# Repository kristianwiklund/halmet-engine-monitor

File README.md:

# Disclaimer

Completely untested, and 99% was written by Claude - I will do more work on this including QA
once spring arrives and it is possible to do work in the actual boat again.

# HALMET Marine Engine & Tank Monitor

Firmware for the [Hat Labs HALMET](https://docs.hatlabs.fi/halmet/) board,
monitoring a **Volvo Penta MD7A** diesel engine via NMEA 2000.

## Features

| Feature | Implementation |
|---|---|
| Engine RPM | Alternator W-terminal pulse counter → PGN 127488 |
| Coolant temperature | INA226 current sensor on shared I2C bus. Derives sender resistance from `V_bus / I_shunt`; maps resistance → °C via runtime-editable VDO Type A NTC curve → PGN 127489 |
| Oil pressure warning | Binary switch on D2 (active-low) → PGN 127489 status bit |
| Temperature warning | Binary switch on D3 (active-low) → PGN 127489 status bit |
| Engine room temps | DS18B20 1-Wire chain on GPIO 4 → PGN 130316 |
| Tank level | Resistive sender (VDO 10–180 Ω) on A2 via 10 mA CCS → PGN 127505; runtime-calibratable curve (Gobius 3-band mode via `-D TANK_SENSOR_GOBIUS`) |
| Battery voltage | Supply voltage on A4 / ADS ch3, 20 kΩ/2.2 kΩ divider → PGN 127508 + SK `electrical.batteries.0.voltage` |
| Bilge fan purge | Relay on GPIO 32; runs after engine stop for configurable time |
| N2K bilge fan switch | PGN 127502 receive (MFD manual on/off) + PGN 127501 Binary Switch Bank Status at 1 Hz |
| Warning lamp | GPIO 33 HIGH when oil or coolant alarm active |
| Ignition key sense | D4 / GPIO 26 (optional) → Signal K `electrical.switches.ignition.state` |

## Hardware Wiring Quick Reference

```
D1 / GPIO 23   ← Alternator W-terminal (via 1 kΩ + diode clamp circuit)
D2 / GPIO 25   ← Oil pressure switch  (one side), other side to GND
D3 / GPIO 27   ← Temp warning switch  (one side), other side to GND
D4 / GPIO 26   ← Ignition key +12 V rail (optional)
A1 / ADS ch0   ← Spare (coolant temp no longer read from A1 — see INA226 below)
A2 / ADS ch1   ← Resistive tank sender (10 mA CCS, VDO 10–180 Ω)  — enable CCS jumper on A2
A3 / ADS ch2   ← Gobius sensor B OUT1 (Gobius mode only, 10 kΩ pull-up to +3.3 V)
A4 / ADS ch3   ← Battery / supply voltage (20 kΩ/2.2 kΩ divider, 0–32 V)
I2C (GPIO 21/22) ← INA226 current sensor (shunt in series with VDO coolant sender)
GPIO 4         ← DS18B20 1-Wire DQ   (pull-up built into HALMET)
GPIO 32        → Bilge fan relay module IN
GPIO 33        → Warning lamp (HIGH when oil/coolant alarm active)
```

See `HALMET_Marine_Engine_Monitor_Design.md` for full electrical details
and commissioning procedures.

## Setup

Before building, copy the secrets template and fill in your network details:

```bash
cp src/secrets.h.example src/secrets.h
# Edit src/secrets.h with your WiFi SSID, password, and Signal K server address
```

`src/secrets.h` is gitignored and will not be committed.

## Build & Flash

```bash
# Install PlatformIO CLI or open in VSCode with PlatformIO IDE extension
pip install platformio

# Build
pio run -e halmet

# Upload (board connected via USB)
pio run -e halmet -t upload

# Monitor serial output
pio device monitor -b 115200
```

## Configuration

All runtime parameters are adjustable via the SensESP web UI at
`http://halmet-engine.local/config` (mDNS) or `http://<board-ip>/config`:

| Parameter | Default | Description |
|---|---|---|
| `/rpm/pulses_per_rev` | 10.0 | W-terminal pulses per crankshaft rev — **calibrate first!** |
| `/rpm/running_threshold` | 200 RPM | RPM above which engine is "running" |
| `/bilge/purge_duration_s` | 600 s | Bilge fan on-time after engine stop |
| `/tank/capacity_l` | 100 L | Tank volume for PGN 127505 |
| `/tank/resistance_curve` | VDO 10–180 Ω | CurveInterpolator: resistance (Ω) → level ratio (0–1). Edit in web UI to match your sender. |
| `/coolant/resistance_curve` | VDO Type A NTC | CurveInterpolator: resistance (Ω) → temperature (°C). Pre-loaded with European VDO curve. User-editable. |
| `/coolant/warn_threshold_c` | 95 °C | Signal K warn notification threshold |
| `/coolant/alarm_threshold_c` | 105 °C | Signal K alarm notification threshold |
| `/voltage/multiplier` | 10.09 | A4 voltage divider multiplier. HALMET uses 20 kΩ/2.2 kΩ → (20+2.2)/2.2 = 10.09. Adjust if resistors differ. |
| `/voltage/sk_path` | `electrical.batteries.0.voltage` | Signal K path for battery voltage output. |
| `/n2k/engine_instance` | 0 | NMEA 2000 engine instance (0–252) |
| `/n2k/product_code` | 100 | N2K product code (requires restart) |
| `/n2k/device_function` | 160 | N2K device function — 160 = Engine Gateway (requires restart) |
| `/n2k/device_class` | 25 | N2K device class — 25 = Propulsion (requires restart) |
| `/n2k/manufacturer_code` | 999 | N2K manufacturer code — 999 = uncertified placeholder (requires restart) |
| `/intervals/rpm_n2k_ms` | 250 ms | PGN 127488 send interval (requires restart) |
| `/intervals/n2k_slow_ms` | 1000 ms | PGN 127489/127505/127501/127508 send interval (requires restart) |
| `/intervals/sk_supplemental_ms` | 5000 ms | Signal K-only data interval (requires restart) |

## RPM Calibration

1. Start the engine.
2. Open `http://halmet-engine.local` or Serial monitor.
3. Compare reported RPM against a handheld optical tachometer.
4. Adjust `/rpm/pulses_per_rev` in the web UI until both agree.
5. For a Paris Rhone 14-V alternator on the MD7A, expect a value in the
   range **10–14** (6 pole pairs × ~1.8–2.3 pulley ratio).

## Project Structure

```
halmet-engine/
├── platformio.ini
├── include/
│   ├── halmet_config.h         Compile-time defaults & pin definitions
│   ├── engine_state.h          Shared EngineState struct & CoolantAlertState enum
│   ├── BilgeFan.h              Bilge fan purge state machine
│   ├── RpmSensor.h             Alternator W-terminal RPM counter
│   ├── N2kSenders.h            NMEA 2000 PGN construction helpers
│   ├── analog_inputs.h         ADS1115 coolant temp & tank level callbacks
│   ├── digital_alarms.h        Oil/temp alarm debounce callbacks
│   ├── engine_state_machine.h  RPM debounce & engine running detection
│   ├── n2k_publisher.h         Periodic N2K PGN send callbacks
│   ├── onewire_setup.h         1-Wire bus scan & sensor-centric dest config
│   └── diagnostics.h           SK heartbeat (uptime, version, reset reason)
└── src/
    ├── main.cpp
    ├── BilgeFan.cpp
    ├── RpmSensor.cpp
    ├── N2kSenders.cpp
    ├── analog_inputs.cpp
    ├── digital_alarms.cpp
    ├── engine_state_machine.cpp
    ├── n2k_publisher.cpp
    ├── onewire_setup.cpp
    └── diagnostics.cpp
```

## Dependencies

Managed automatically by PlatformIO from `platformio.ini`:

| Library | Source | Notes |
|---|---|---|
| SensESP v3 | `SignalK/SensESP @ ^3.1.0` | PlatformIO registry |
| NMEA2000-library | `ttlappalainen/NMEA2000-library` | Registry name has a **hyphen** |
| NMEA2000_esp32 | GitHub URL | Not in registry — pulled directly |
| esp_websocket_client | IDF Component Registry URL | IDF 5.x managed component |
| SensESP/OneWire | `SensESP/OneWire @ ^3.0.1` | Replaces raw OneWire + DallasTemperature |
| Adafruit ADS1X15 | `adafruit/Adafruit ADS1X15 @ ^2.5` | PlatformIO registry |
| INA226_WE | `wollewald/INA226_WE` | I2C current/voltage sensor for coolant sender resistance measurement |

## Troubleshooting

### `UnknownPackageError: Could not find the package with 'ttlappalainen/NMEA2000 @ ^4.19'`

Three separate issues were present in the original configuration — all fixed in the current `platformio.ini`:

**1. Wrong NMEA2000 library name**
The PlatformIO registry name is `ttlappalainen/NMEA2000-library` (with a hyphen). The name `ttlappalainen/NMEA2000` does not exist in the registry. Additionally, the library uses a date-based version scheme — there is no version `4.19`, so the `@ ^4.19` specifier also fails. Omitting the version constraint lets PlatformIO pick the latest published release.

```ini
; ❌ Wrong — does not exist in registry
ttlappalainen/NMEA2000 @ ^4.19

; ✅ Correct
ttlappalainen/NMEA2000-library
```

**2. Wrong `NMEA2000_esp32` specifier**
The ESP32 TWAI/CAN driver is not published to the PlatformIO registry at all, so `ttlappalainen/NMEA2000_esp32 @ ^1.0` also fails with `UnknownPackageError`. It must be pulled directly from GitHub:

```ini
; ❌ Wrong — not in registry
ttlappalainen/NMEA2000_esp32 @ ^1.0

; ✅ Correct
https://github.com/ttlappalainen/NMEA2000_esp32.git
```

**3. Wrong platform for SensESP v3**
SensESP v3 requires Arduino ESP32 Core 3.x (ESP-IDF 5.x). The official PlatformIO `espressif32` platform is frozen at Core 2.0.17 (Espressif ended support for the official PlatformIO platform in late 2023 after the Core 3.x release). The SensESP project itself uses the community **pioarduino** fork:

```ini
; ❌ Wrong — frozen at Arduino Core 2.0.17, incompatible with SensESP v3
platform = espressif32

; ✅ Correct — pioarduino, tracks Arduino Core 3.x releases
platform = https://github.com/pioarduino/platform-espressif32/releases/download/stable/platform-espressif32.zip
```

Note that pioarduino also requires two additional `build_flags` that SensESP v3 needs:
```ini
build_flags =
    -D USE_ESP_IDF_LOG
    -D CORE_DEBUG_LEVEL=ARDUHAL_LOG_LEVEL_WARN
```

### `fatal error: esp_websocket_client.h: No such file or directory`

In ESP-IDF 4.x, `esp_websocket_client` was bundled with the SDK. In IDF 5.x (pioarduino) it became a separately managed component. Declare it in `lib_deps` using the `name=url` syntax so PlatformIO registers it as a named IDF component:

```ini
lib_deps =
    esp_websocket_client=https://components.espressif.com/api/downloads/?object_type=component&object_id=dbc87006-9a4b-45e6-a6ab-b286174cb413
```

Note the `name=` prefix — a bare URL without it causes the component to be treated as an anonymous download and not wired into the IDF component build system correctly.

### `fatal error: OneWire.h: No such file or directory` / `sensesp.h` / `NMEA2000.h`

All three share the same root cause: PlatformIO's default Library Dependency Finder mode is `chain`, which only scans one level of `#include` directives. It reads your `src/` files, finds the libraries they include directly, but **stops there** — it does not recurse into those libraries' own headers.

`OneWire.h`, `sensesp.h`, and `NMEA2000.h` are all included from **inside** library headers (not directly from `src/`), so LDF in `chain` mode never discovers them.

The fix is two lines:

```ini
; Recurse into all library headers to find transitive dependencies
lib_ldf_mode = deep

; Link object files directly — required by pioarduino (weak-symbol handling)
lib_archive = no
```

`lib_ldf_mode = deep` makes LDF recurse into every header of every library it finds, so transitive dependencies are discovered automatically. `lib_archive = no` is a separate but related pioarduino requirement: without it the linker discards weak-symbol overrides in the ESP-IDF framework, causing obscure link failures after compilation succeeds.

## License

MIT — see `LICENSE`.

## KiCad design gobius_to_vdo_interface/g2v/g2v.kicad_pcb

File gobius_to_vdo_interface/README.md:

# Design files for a gobius-to-vdo interface

NOT tested yet!

The schematics png is a screenshot from the kicad files in the g2v subdirectory.

The basic principle is that the gobiusen are switching in and out resistors in a resistance ladder, thus emulating a standard resistive instrument.

- R4 / R6 - must be dimensioned to not burn out the open collector output on the gobiusen or the led in the opto, and at the same time provide enough current to the optos to switch them.
    - https://forums.raspberrypi.com/viewtopic.php?t=355542
    - https://learnabout-electronics.org/Semiconductors/opto_52.php
    -  https://www.farnell.com/datasheets/73758.pdf -> 2-4 mA is enough

- LA1 is a "lamp" - can be a LED with a resistor or a ready-made "led lamp" with a resistor / current draw not exceeding the opto specs. I've ordered one of these -> https://s.click.aliexpress.com/e/_c4oVMiaf (affiliate link)

- The device is connected to the Halmet using active resistance measuring mode, see https://docs.hatlabs.fi/halmet/docs/usage/

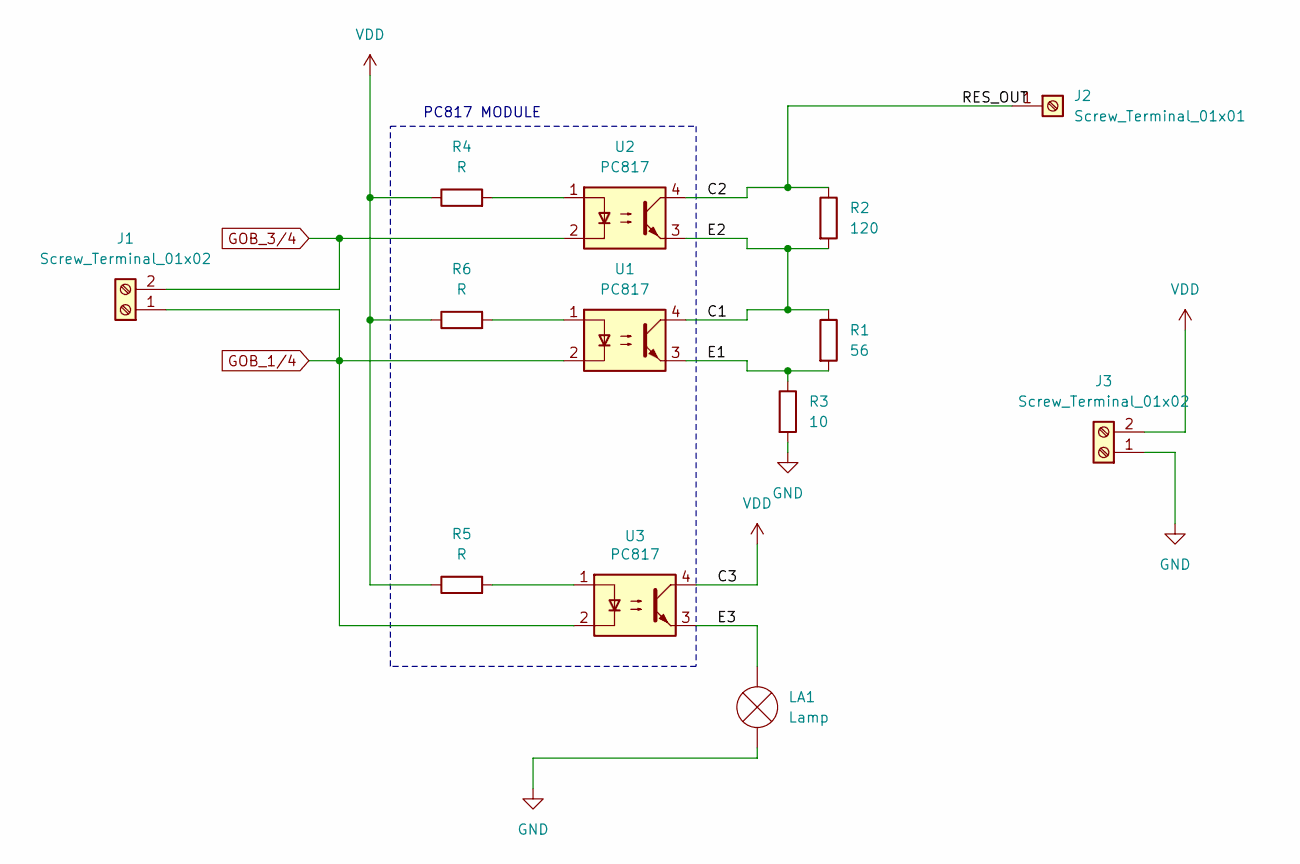
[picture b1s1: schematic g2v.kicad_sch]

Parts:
J1, J3: Screw_Terminal_01x02; TerminalBlock_MaiXu_MX126-5.0-02P_1x02_P5.00mm
J2: Screw_Terminal_01x01; TerminalBlock_Degson_DG250-3.5-01P_1x01_P3.50mm_45Degree
LA1: Lamp; TerminalBlock_MaiXu_MX126-5.0-02P_1x02_P5.00mm
R1: 56; R_Axial_DIN0204_L3.6mm_D1.6mm_P5.08mm_Horizontal
R2: 120; R_Axial_DIN0204_L3.6mm_D1.6mm_P5.08mm_Horizontal
R3: 10; R_Axial_DIN0204_L3.6mm_D1.6mm_P5.08mm_Horizontal
R4, R5, R6: R; R_Axial_DIN0204_L3.6mm_D1.6mm_P5.08mm_Horizontal
U1, U2, U3: PC817; DIP-4_W7.62mm

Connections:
/C1: R1.1, R2.2, U1.4, U2.3
/C2: J2.1, R2.1, U2.4
/E1: R1.2, R3.1, U1.3
/E3: LA1.2 (+), U3.3
GND: J3.1, LA1.1 (-), R3.2
GOB_1/4: J1.1, U1.2, U3.2
GOB_3/4: J1.2, U2.2
unnamed: R4.2, U2.1
unnamed: R5.2, U3.1
unnamed: R6.2, U1.1
VDD: J3.2, R4.1, R5.1, R6.1, U3.4

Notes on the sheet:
PC817 MODULE

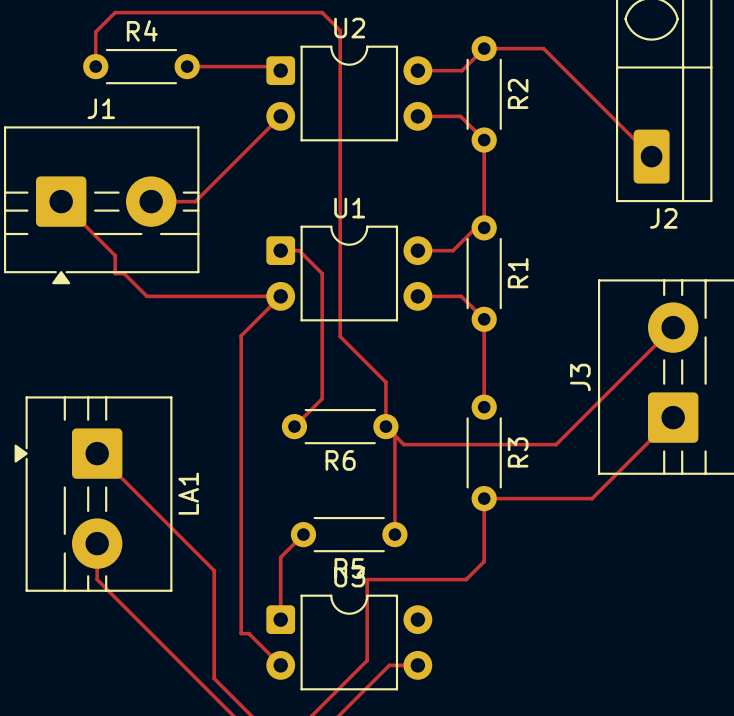
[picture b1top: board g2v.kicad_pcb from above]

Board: 2 copper layers, 13 parts (0 on the bottom side), 11 nets.

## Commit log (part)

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2026-02-14 Specs etc
2026-02-15 Experiments with pio check
2026-02-15 added a gobius to vdo (resistive interface) for two gobiuses. (Created by google gemini - not tested yet)
2026-02-15 added links about alternator rpm sensing
2026-02-15 moved gobius interface to own dir
2026-02-15 updated ali link
2026-02-15 readme for gobius
2026-02-15 added gobius AI-generated schematic - likely wrong
2026-02-28 added kicad for gobius interface
2026-02-28 cleanup
2026-02-28 readme for the gobius interface
2026-02-28 updated gobius interface readme
2026-03-04 gitignore
2026-03-06 bugfix in path metadata
2026-04-16 Sprint 11 quick wins: #31 #32 #34 #37
    #31 — Stop polling NVS after first N2K address save
    #32 — Replace magic numbers in setupNmea2000() with named constants
    #34 — Extract SwitchMetadata to include/SwitchMetadata.h
    #37 — Document EngineState single-task thread-safety invariant
    Also adds Sprint 11 backlog items (#27-#37) to roadmap.md.
    No functional changes. Build verified.
2026-04-16 #28 — Fix bilge fan manual override not cleared on engine start
    manualOn() latched the relay ON, but the latch was never cleared
    when the engine started. This caused the fan to run through the
    entire RUNNING state, violating the design invariant that the
    relay is never energised while the engine is running.
    Fix: unconditionally clear _manualOverride and force relay off
    on every transition into RUNNING (from IDLE, RUNNING tick, and
2026-04-16 #29 — Decouple RPM N2K send rate from measurement rate
    Split engine_state_machine callback: RPM measurement stays at
    10 Hz (INTERVAL_RPM_MS), PGN 127488 send now at 4 Hz
    (INTERVAL_RPM_N2K_MS 250 ms). Cuts RPM bus load by 60%.
    Also moved remaining inline magic interval numbers to named
    defines in halmet_config.h: INTERVAL_N2K_SLOW_MS,
    INTERVAL_N2K_PUMP_MS, INTERVAL_SK_SUPPLEMENTAL_MS.
2026-04-16 Add candidate pool items: web UI configurable send intervals and N2K device constants
2026-04-16 Move Sprint 7 items #18 #19 to candidate pool, normalize line endings
2026-04-16 #27 — Hardware watchdog (consolidated from Sprint 5 #12)
    Register ESP32 task watchdog with 8 s timeout (WATCHDOG_TIMEOUT_MS).
    Reset in loop() each tick. Deregister from TWDT in ArduinoOTA.onStart
    before relay forceOff, so OTA can block for 30-90 s without triggering
    a panic. trigger_panic=true ensures a full reboot on hang.
    Also merges Sprint 5 #12 into Sprint 11 #27 in roadmap.
2026-04-16 Mark Sprint 4 (#13 #14) as complete — done in commit f48dd79
2026-04-16 #35 — Update backlog: FW_VERSION_STR derived from git tag
2026-04-16 #30 #33 #35 — RPM single-instance guard, OTA password from secrets.h, version from git tag
    #30 — Add static bool guard in RpmSensor::begin() to prevent
    silent state sharing if instantiated twice.
    #33 — OTA password now read from OTA_PASSWORD in secrets.h.
    Fallback: pre-build script generates a random password
    (OTA protected but unreachable until user sets a real one).
    Updated secrets.h.example with OTA_PASSWORD template.
2026-04-16 #36 — Add Signal K output for Gobius tank mode
    Gobius path now publishes to tanks.fuel.0.currentLevel as ratio
    0-1, matching the resistive sender path. N2K output (percentage
    via st->tankLevelPct) was already working.
2026-04-16 Move configurable N2K engine instance from candidate pool to Sprint 12 (#38)
2026-04-16 Move configurable send intervals (#39) and N2K device constants (#40) from candidate pool to Sprint 12
2026-04-16 Add battery voltage sensing (#41) and coolant temp ratio correction (#42) to Sprint 12
    Promotes battery voltage from candidate pool. #42 depends on #41
    for supply voltage reference.
2026-04-16 Split Sprint 12: web UI config (#38-40) and battery voltage + temp accuracy (#41-42) into Sprint 13
2026-04-16 Move runtime-configurable temp curve from candidate pool to Sprint 13 (#43)
2026-04-16 #43 — Detail: VDO Type A/B base curves, zero gauge resistance assumption, user fine-tuning
2026-04-16 Sprint 12: #38 #39 #40 — Web UI configurable N2K and interval parameters
    #38 — N2K engine instance configurable via web UI (/n2k/engine_instance).
    Threaded through to engine_state_machine and n2k_publisher.
    #39 — Send intervals configurable via web UI (requires restart):
    PGN 127488 rate, slow PGN rate, SK supplemental rate.
    #40 — N2K device constants configurable via web UI (requires restart):
    product code, device function, device class, manufacturer code.
2026-04-16 #42 #43 — Archive assumptions, reset temp sender design to clean slate
2026-04-16 #42 #43 — Redesign: INA226 current sensor for coolant temp, A1 retired
2026-04-16 Sprint 13: #41 #42 #43 — Battery voltage, INA226 coolant temp, VDO curve
    #41 — Battery voltage on A4 (ADS ch3, 20k/2.2k divider = 10.09:1).
    Configurable multiplier in web UI. PGN 127508 + SK output.
    #42 — Coolant temp via INA226 on shared I2C bus. Derives sender
    resistance from V_bus / I_shunt. Replaces A1 voltage-based
    measurement entirely.
    #43 — CurveInterpolator for resistance→°C mapping. Pre-populated
2026-06-29 chores: PIO update and secrets placeholder
